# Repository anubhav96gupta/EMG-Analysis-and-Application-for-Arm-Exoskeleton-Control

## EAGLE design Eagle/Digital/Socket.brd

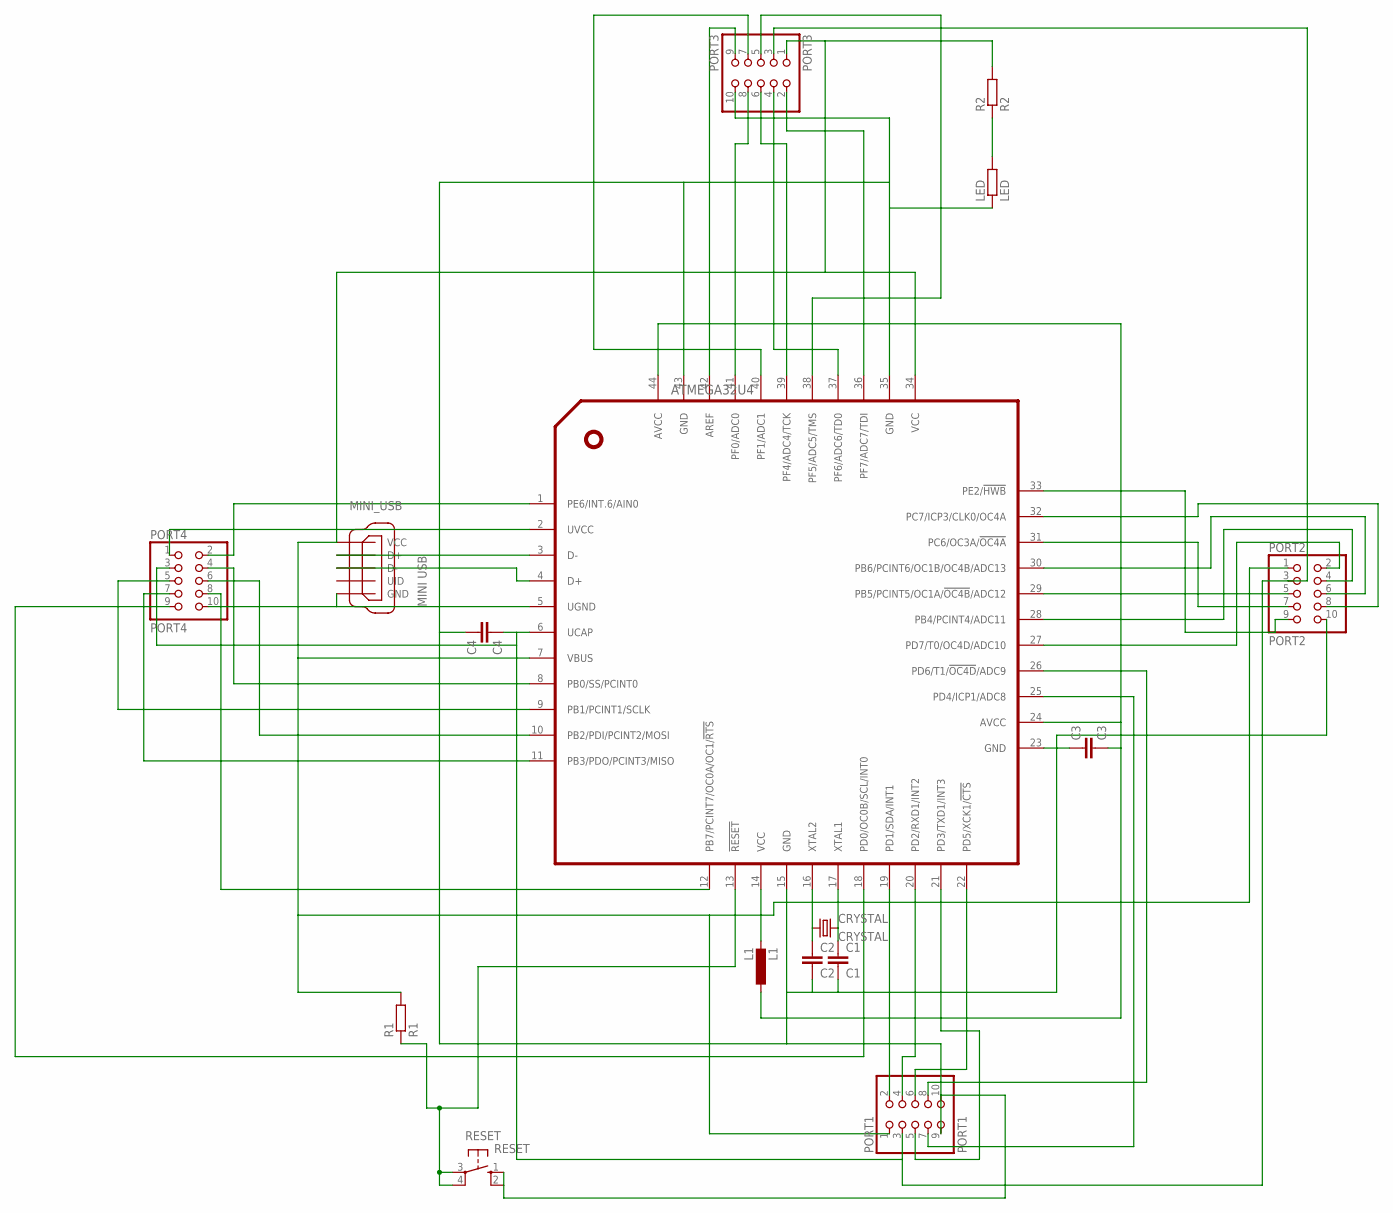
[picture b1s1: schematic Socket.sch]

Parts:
ATMEGA32U4: ATMEGA32U4; TQFP44
C1: C1; C0603
C2: C2; C0603
C3: C3; C0603
C4: C4; C0603
CRYSTAL: CRYSTAL; HC49UP
L1: L1; L2012C
LED: LED; R0603
MINI_USB: MINI USB; UX60-MB-5S8
PORT1: PORT1; 2X05
PORT2: PORT2; 2X05
PORT3: PORT3; 2X05
PORT4: PORT4; 2X05
R1: R1; R0603
R2: R2; R0603
RESET: RESET; B3F-10XX

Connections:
3.3VCC: ATMEGA32U4.6 (UCAP), C4.1, PORT1.3, PORT2.3, PORT3.3, PORT4.3
5VCC: ATMEGA32U4.2 (UVCC), ATMEGA32U4.7 (VBUS), ATMEGA32U4.14 (VCC), ATMEGA32U4.34 (VCC), L1.2, MINI_USB.VCC, PORT1.1, PORT2.1, PORT3.1, PORT4.1, R1.2, R2.2
D+: ATMEGA32U4.4 (D+), MINI_USB.D-
GND: ATMEGA32U4.5 (UGND), ATMEGA32U4.15 (GND), ATMEGA32U4.23 (GND), ATMEGA32U4.35 (GND), ATMEGA32U4.43 (GND), C1.2, C2.2, C3.1, C4.2, LED.1, MINI_USB.GND, MINI_USB.GND1 (GND), MINI_USB.GND2 (GND), MINI_USB.GND3 (GND), MINI_USB.GND4 (GND), PORT1.9, PORT1.10, PORT2.10, PORT3.10, PORT4.10, RESET.1 (S), RESET.2 (S1)
unnamed: ATMEGA32U4.16 (XTAL2), C2.1, CRYSTAL.1
unnamed: ATMEGA32U4.17 (XTAL1), C1.1, CRYSTAL.2
unnamed: ATMEGA32U4.1 (PE6/INT.6/AIN0), PORT4.2
unnamed: LED.2, R2.1
unnamed: ATMEGA32U4.24 (AVCC), ATMEGA32U4.44 (AVCC), C3.2, L1.1
unnamed: ATMEGA32U4.8 (PB0/SS/PCINT0), PORT4.4
unnamed: ATMEGA32U4.9 (PB1/PCINT1/SCLK), PORT4.5
unnamed: ATMEGA32U4.3 (D-), MINI_USB.D+
unnamed: ATMEGA32U4.13 (!RESET), R1.1, RESET.3, RESET.4 (P1)
unnamed: ATMEGA32U4.10 (PB2/PDI/PCINT2/MOSI), PORT4.6
unnamed: ATMEGA32U4.11 (PB3/PDO/PCINT3/MISO), PORT4.7
unnamed: ATMEGA32U4.12 (PB7/PCINT7/OC0A/OC1/!RTS), PORT4.8
unnamed: ATMEGA32U4.18 (PD0/OC0B/SCL/INT0), PORT4.9
unnamed: ATMEGA32U4.19 (PD1/SDA/INT1), PORT1.2
unnamed: ATMEGA32U4.20 (PD2/RXD1/INT2), PORT1.4
unnamed: ATMEGA32U4.21 (PD3/TXD1/INT3), PORT1.5
unnamed: ATMEGA32U4.22 (PD5/XCK1/!CTS), PORT1.6
unnamed: ATMEGA32U4.25 (PD4/ICP1/ADC8), PORT1.7
unnamed: ATMEGA32U4.26 (PD6/T1/!OC4D!/ADC9), PORT1.8
unnamed: ATMEGA32U4.36 (PF7/ADC7/TDI), PORT3.2
unnamed: ATMEGA32U4.27 (PD7/T0/OC4D/ADC10), PORT2.2
unnamed: ATMEGA32U4.28 (PB4/PCINT4/ADC11), PORT2.4
unnamed: ATMEGA32U4.29 (PB5/PCINT5/OC1A/!OC4B!/ADC12), PORT2.5
unnamed: ATMEGA32U4.30 (PB6/PCINT6/OC1B/OC4B/ADC13), PORT2.6
unnamed: ATMEGA32U4.31 (PC6/OC3A/!OC4A), PORT2.7
unnamed: ATMEGA32U4.32 (PC7/ICP3/CLK0/OC4A), PORT2.8
unnamed: ATMEGA32U4.33 (PE2/!HWB), PORT2.9
unnamed: ATMEGA32U4.37 (PF6/ADC6/TD0), PORT3.4
unnamed: ATMEGA32U4.38 (PF5/ADC5/TMS), PORT3.5
unnamed: ATMEGA32U4.40 (PF1/ADC1), PORT3.7
unnamed: ATMEGA32U4.41 (PF0/ADC0), PORT3.8
unnamed: ATMEGA32U4.42 (AREF), PORT3.9
PORT3: ATMEGA32U4.39 (PF4/ADC4/TCK), PORT3.6

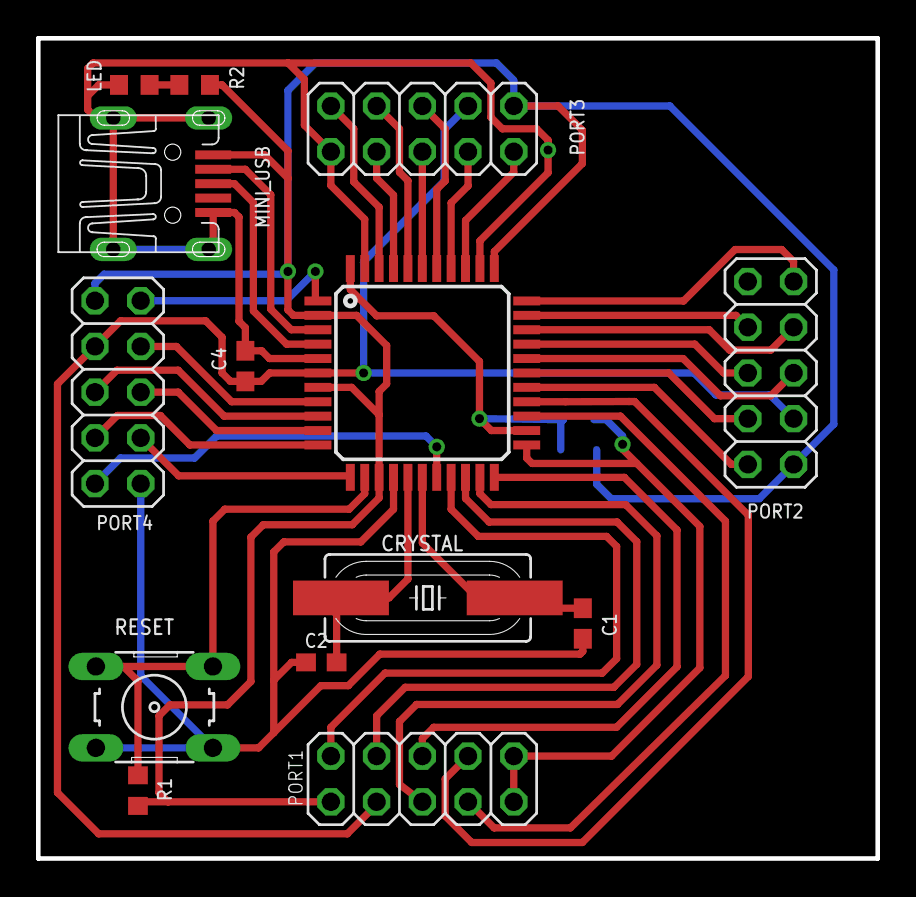
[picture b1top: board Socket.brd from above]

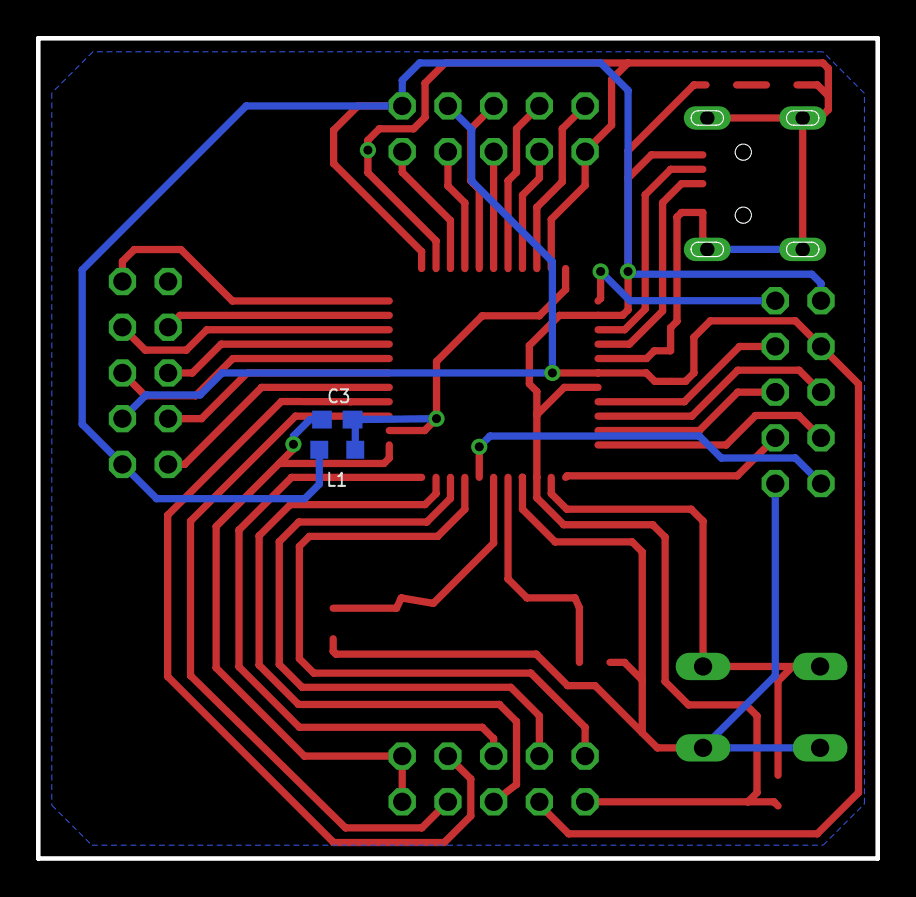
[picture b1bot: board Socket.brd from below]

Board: 2 copper layers, 46.6 x 45.6 mm, 16 parts (2 on the bottom side), 37 nets.

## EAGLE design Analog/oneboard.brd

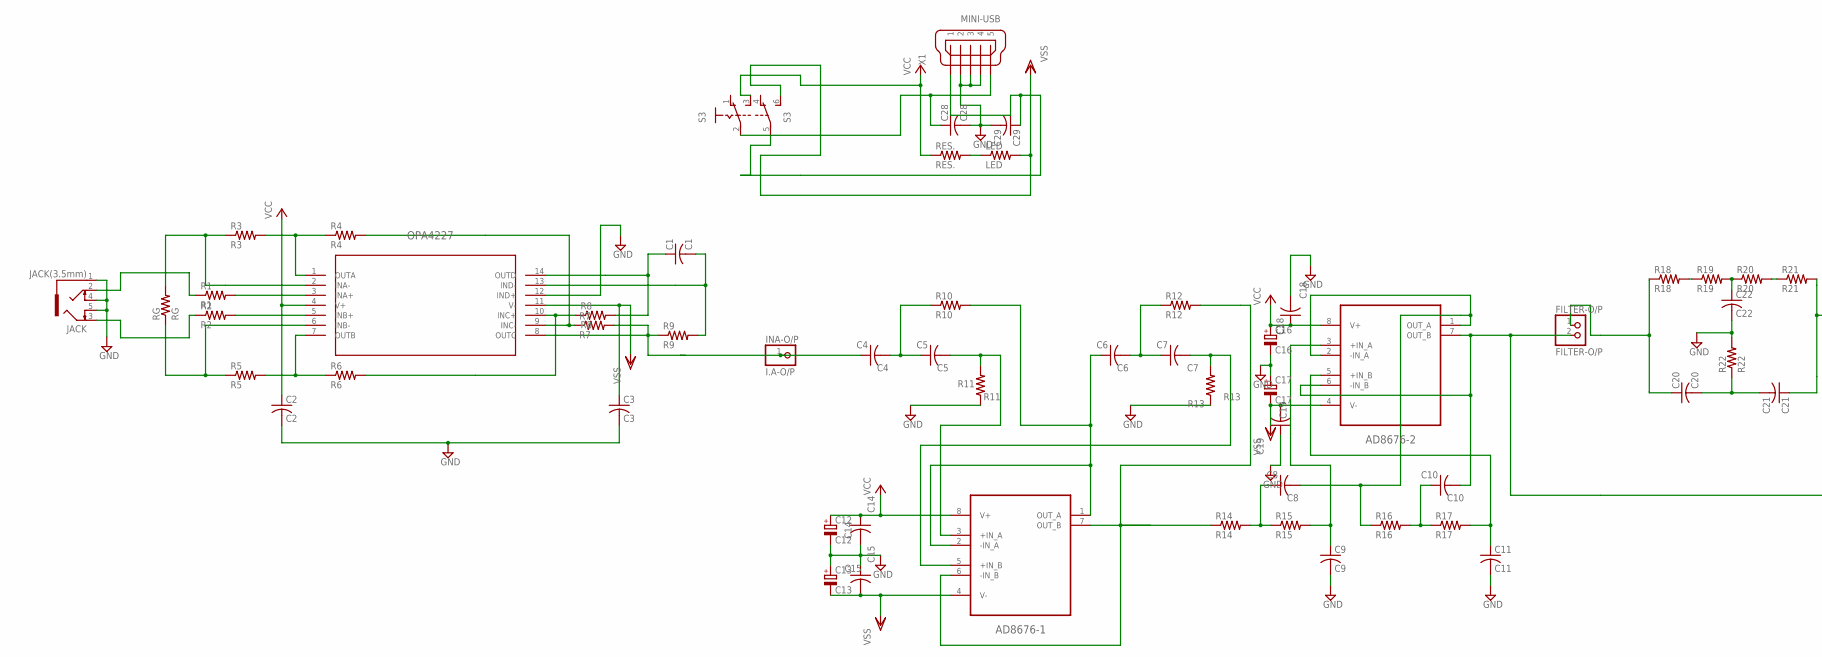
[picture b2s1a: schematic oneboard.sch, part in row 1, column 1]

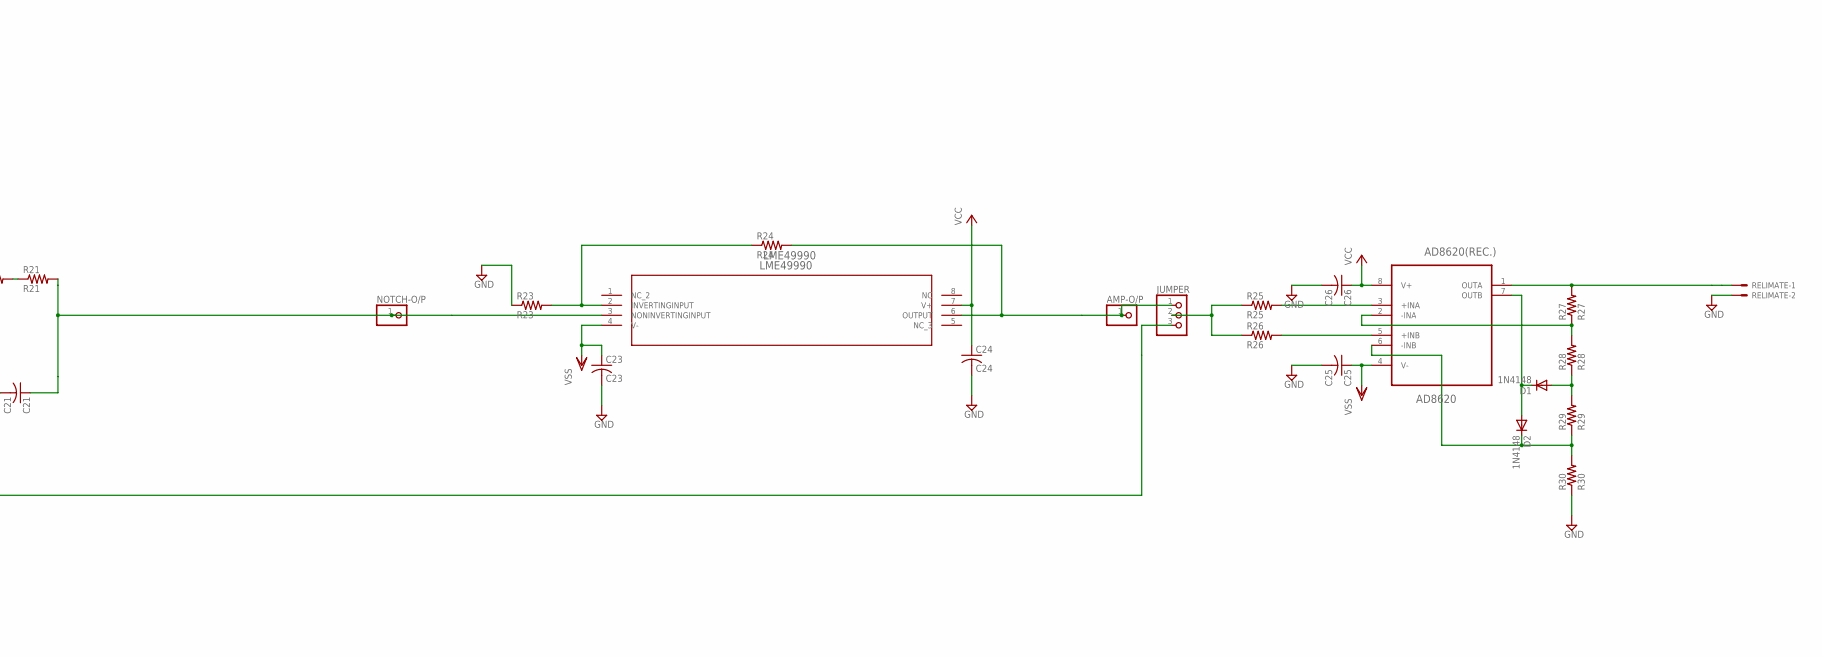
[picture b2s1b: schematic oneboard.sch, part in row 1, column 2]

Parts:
AD8620(REC.): AD8620; SOIC127P600X175-8N
AD8676-1: AD8676-1; SOIC127P600X175-8N
AD8676-2: AD8676-2; SOIC127P600X175-8N
AMP-O/P: PINHD-1X1; 1X01
C1: C1; C0603
C2: C2; C0603
C3: C3; C0603
C4: C4; C0603
C5: C5; C0603
C6: C6; C0603
C7: C7; C0603
C8: C8; C0603
C9: C9; C0603
C10: C10; C0603
C11: C11; C0603
C12: C12; E2-5
C13: C13; E2-5
C14: C14; C0603
C15: C15; C0603
C16: C16; E2-5
C17: C17; E2-5
C18: C18; C0603
C19: C19; C0603
C20: C20; C0603
C21: C21; C0603
C22: C22; C0603
C23: C23; C0603
C24: C24; C0603
C25: C25; C0603
C26: C26; C0603
C28: C28; C0603
C29: C29; C0603
D1, D2: 1N4148; DO35-10
FILTER-O/P: FILTER-O/P; 1X02
INA-O/P: I.A-O/P; 1X01
JACK: JACK(3.5mm); 1503_09
JUMPER: PINHD-1X3; 1X03
LED: LED; R0805
LME49990: LME49990; M08A
NOTCH-O/P: PINHD-1X1; 1X01
OPA4227: OPA4277_D_14; D14
R1: R1; R0603
R2: R2; R0603
R3: R3; R0603
R4: R4; R0603
R5: R5; R0603
R6: R6; R0603
R7: R7; R0603
R8: R8; R0603
R9: R9; R0603
R10: R10; R0603
R11: R11; R0603
R12: R12; R0603
R13: R13; R0603
R14: R14; R0603
R15: R15; R0603
R16: R16; R0603
R17: R17; R0603
R18: R18; R0603
R19: R19; R0603
R20: R20; R0603
R21: R21; R0603
R22: R22; R0603
R23: R23; R0603
R24: R24; R0603
R25: R25; R0603
R26: R26; R0603
R27: R27; R0603
R28: R28; R0603
R29: R29; R0603
R30: R30; R0603
RELIMATE: 22-23-2021
RES.: RES.; R0603
RG: RG; R0603
S3: A68-A31
X1: MINI-USB; UX60-MB-5S8

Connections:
1: C21.1, LME49990.3 (NONINVERTINGINPUT), NOTCH-O/P.1, R21.2
5: C29.1, S3.5, X1.1
GND: C2.2, C3.2, C9.2, C11.2, C12.-, C13.+, C14.2, C15.1, C16.-, C17.+, C18.2, C19.1, C22.2, C23.2, C24.2, C25.2, C26.2, C28.2, C29.2, JACK.1, JACK.4, JACK.5, OPA4227.12 (IND+), R11.1, R13.1, R22.2, R23.1, R30.1, RELIMATE.2, X1.2, X1.3, X1.4
H-O/P: AD8676-1.6 (-IN_B), AD8676-1.7 (OUT_B), R12.2, R14.1
unnamed: OPA4227.3 (INA+), R1.2
unnamed: OPA4227.5 (INB+), R2.2
unnamed: JACK.3, R2.1
unnamed: JACK.2, R1.1
unnamed: OPA4227.1 (OUTA), R3.2, R4.1
unnamed: OPA4227.2 (INA-), R3.1, RG.2
unnamed: OPA4227.9 (INC-), R4.2, R7.1
unnamed: OPA4227.6 (INB-), R5.1, RG.1
unnamed: OPA4227.10 (INC+), R6.2, R8.1
unnamed: C1.2, OPA4227.13 (IND-), R9.2
unnamed: C4.2, C5.1, R10.1
unnamed: C1.1, OPA4227.14 (OUTD), R8.2
unnamed: C4.1, INA-O/P.1, OPA4227.8 (OUTC), R7.2, R9.1
unnamed: AD8676-1.3 (+IN_A), C5.2, R11.2
unnamed: AD8676-1.1 (OUT_A), AD8676-1.2 (-IN_A), C6.1, R10.2
unnamed: C6.2, C7.1, R12.1
unnamed: AD8676-1.5 (+IN_B), C7.2, R13.2
unnamed: C8.1, R14.2, R15.1
unnamed: AD8676-2.3 (+IN_A), C9.1, R15.2
unnamed: C10.1, R16.2, R17.1
unnamed: AD8676-2.5 (+IN_B), C11.1, R17.2
unnamed: AD8676-2.1 (OUT_A), AD8676-2.2 (-IN_A), C8.2, R16.1
unnamed: AD8620(REC.).3 (+INA), R25.2
unnamed: C22.1, R19.2, R20.1
unnamed: LED.1, RES..2
unnamed: C20.2, C21.2, R22.1
unnamed: R18.2, R19.1
unnamed: R20.2, R21.1
unnamed: AD8620(REC.).5 (+INB), R26.2
unnamed: JUMPER.2, R25.1, R26.1
unnamed: AD8676-2.6 (-IN_B), AD8676-2.7 (OUT_B), C10.2, FILTER-O/P.2, JUMPER.3
unnamed: C20.1, FILTER-O/P.1, R18.1
unnamed: AD8620(REC.).2 (-INA), R27.1, R28.2
unnamed: AD8620(REC.).1 (OUTA), R27.2, RELIMATE.1
unnamed: D1.A, R28.1, R29.2
unnamed: AD8620(REC.).6 (-INB), D2.C, R29.1, R30.2
unnamed: AD8620(REC.).7 (OUTB), D1.C, D2.A
unnamed: LME49990.2 (INVERTINGINPUT), R23.2, R24.1
unnamed: AMP-O/P.1, JUMPER.1, LME49990.6 (OUTPUT), R24.2
unnamed: C28.1, S3.2, X1.5
R6: OPA4227.7 (OUTB), R5.2, R6.1
VCC: AD8620(REC.).8 (V+), AD8676-1.8 (V+), AD8676-2.8 (V+), C2.1, C12.+, C14.1, C16.+, C18.1, C24.1, C26.1, LME49990.7 (V+), OPA4227.4 (V+), RES..1, S3.3 (S)
VSS: AD8620(REC.).4 (V-), AD8676-1.4 (V-), AD8676-2.4 (V-), C3.1, C13.-, C15.2, C17.-, C19.2, C23.1, C25.1, LED.2, LME49990.4 (V-), OPA4227.11 (V-), S3.6 (S)

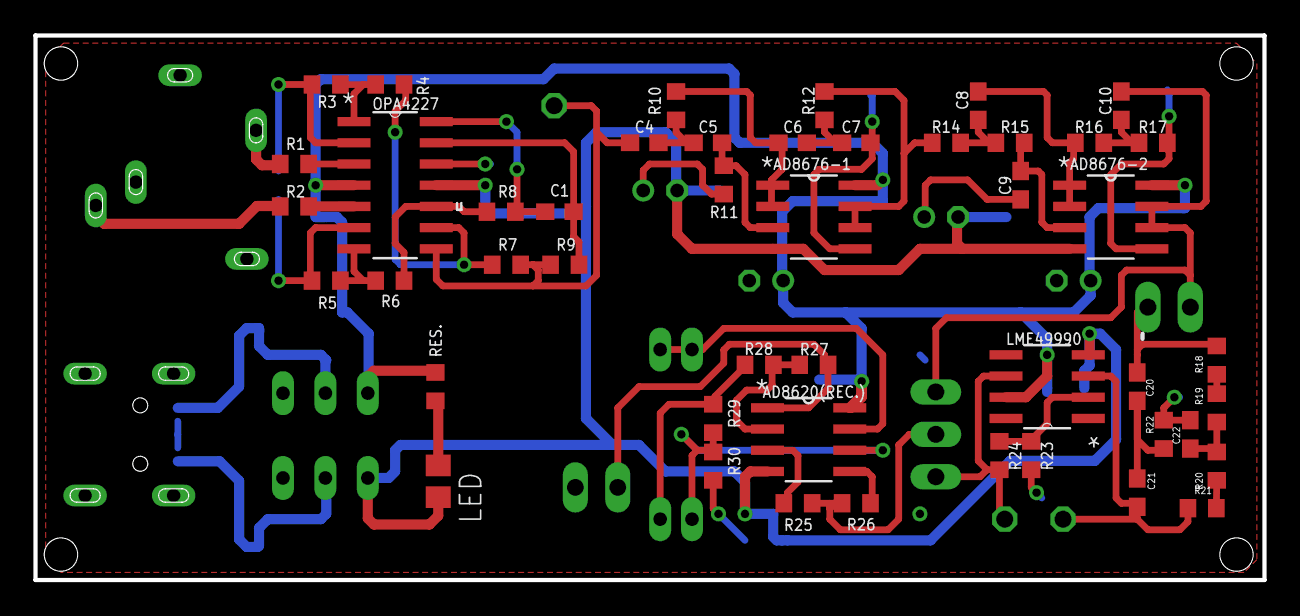
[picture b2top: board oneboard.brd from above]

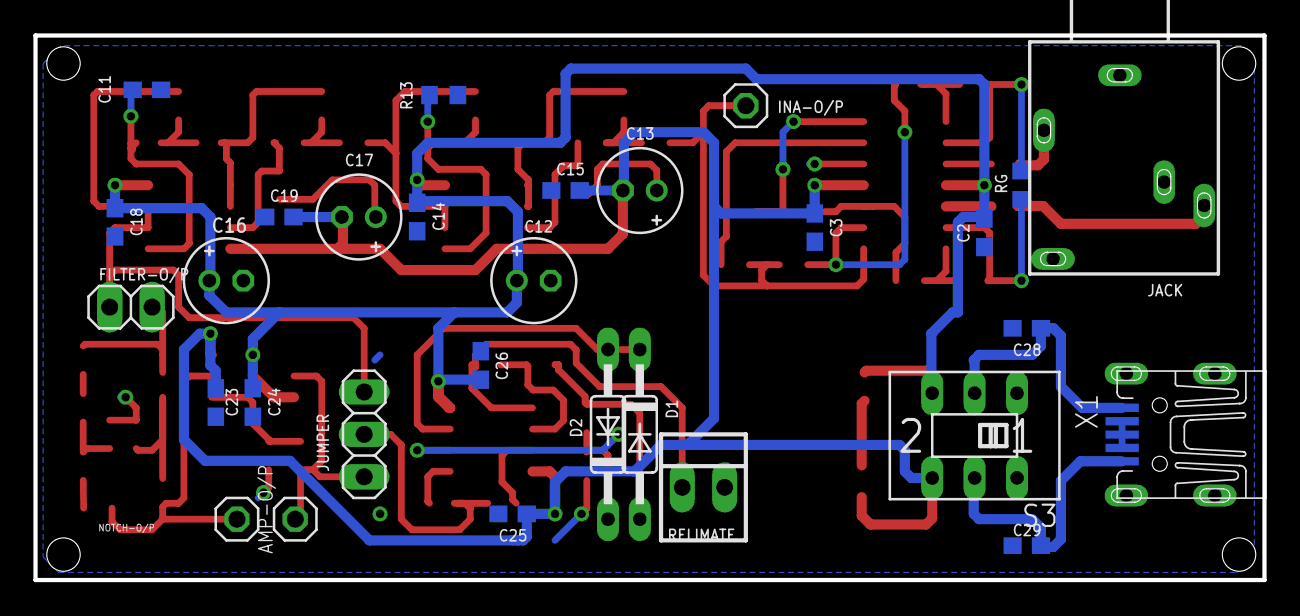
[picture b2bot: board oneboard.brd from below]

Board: 2 copper layers, 73.6 x 32.6 mm, 77 parts (30 on the bottom side), 47 nets.

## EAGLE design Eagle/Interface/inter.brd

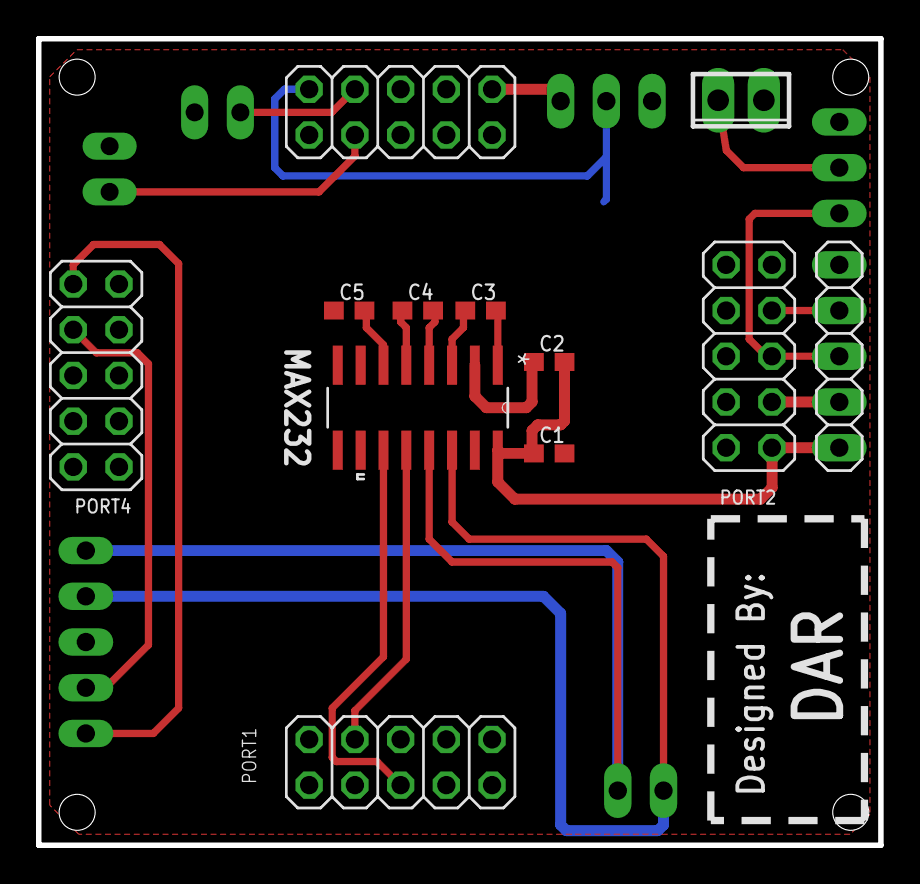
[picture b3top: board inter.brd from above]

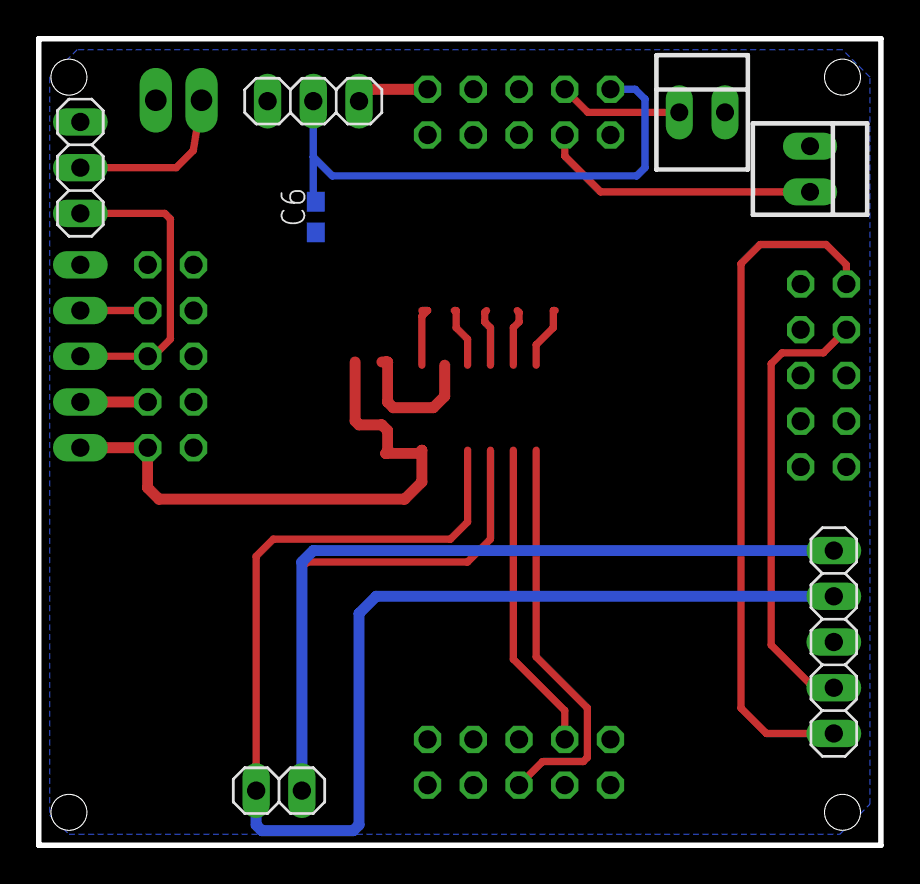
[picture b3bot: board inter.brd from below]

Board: 2 copper layers, 46.8 x 44.8 mm, 19 parts (7 on the bottom side), 23 nets.

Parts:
ADC-0, ADC-1: 22-23-2021
C1: C1; C0603
C2: C2; C0603
C3: C3; C0603
C4: C4; C0603
C5: C5; C0603
C6: C6; C0603
MAX232: MAX232; D16
MOTOR-SUPPLY: 2POL254
PORT1: PORT1; 2X05
PORT2: PORT2; 2X05
PORT3: PORT3; 2X05
PORT4: PORT4; 2X05
RX/TX: 1X02
SERVO: 1X03
SUPPLY: 1X05
VREF: 1X03
ZIGBEE: 1X05

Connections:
ADC-0: ADC-0.2, PORT3.8
C4: C4.2, MAX232.4
GND: ADC-0.1, ADC-1.2, C1.2, C5.1, C6.1, MOTOR-SUPPLY.1, PORT1.10, PORT2.10, PORT4.10, SERVO.1, VREF.1
S$1: C3.1, MAX232.3
S$2: C3.2, MAX232.1
S$4: C4.1, MAX232.5
S$6: PORT4.1, ZIGBEE.5
S$7: C1.1, C2.2, MAX232.16
S$8: C2.1, MAX232.2
S$9: C5.2, MAX232.6
S$10: C6.2, PORT3.9, VREF.2
S$11: MAX232.11, PORT1.5
S$12: MAX232.12, PORT1.4
S$13: PORT2.1, SUPPLY.1
S$14: PORT2.3, SUPPLY.2
S$15: PORT2.5, SERVO.3, SUPPLY.3
S$16: PORT2.7, SUPPLY.4
S$17: MOTOR-SUPPLY.2, SERVO.2
S$18: MAX232.13, RX/TX.1, ZIGBEE.1
S$19: MAX232.14, RX/TX.2, ZIGBEE.2
S$21: ADC-1.1, PORT3.7
S$23: PORT3.1, VREF.3
S$24: PORT4.3, ZIGBEE.4

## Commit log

2016-12-27 Adding Project To Git
